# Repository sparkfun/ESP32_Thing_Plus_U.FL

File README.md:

SparkFun ESP32 Thing Plus (U.FL)
========================================

[*SparkFun ESP32 Thing Plus U.FL (WRL-18581)*](https://www.sparkfun.com/products/18581)

The [SparkFun ESP32 Thing Plus (U.FL)](https://www.sparkfun.com/products/18581) is a comprehensive development platform for [Espressif's ESP32](https://espressif.com/en/products/hardware/esp32/overview). This board has the ESP32-WROOM-32EU version of the module which contains a U.FL connector for your antenna. Like the 8266 and ESP32 Thing, the ESP32 Thing Plus is a **WiFi**-compatible microcontroller with support for **Bluetooth low-energy** (i.e BLE, BT4.0, Bluetooth Smart), a Qwiic adapter, and 21 I/O pins. Add to that a rich set of peripherals ranging from capacitive touch sensors, SD card interface, Ethernet, high-speed SPI, UART, I2S and I<sup>2</sup>C.

Upgraded and easy to use, the Esp32 Thing Plus will help make it the foundation of IoT and connected projects for many years to come.

Repository Contents
-------------------

* **/Hardware** - Eagle design files (.brd, .sch)
* **/Hardware/Production** - Production panel files (gerbers, .brd)

Documentation
--------------
* **[Hookup Guide](https://learn.sparkfun.com/tutorials/esp32-thing-plus-hookup-guide)** - Basic hookup guide for the ESP32 Thing Plus.
* **[SparkFun Fritzing repo](https://github.com/sparkfun/Fritzing_Parts)** - Fritzing diagrams for SparkFun products.
* **[SparkFun Graphical Datasheets](https://github.com/sparkfun/Graphical_Datasheets)** -Graphical Datasheets for various SparkFun products.

Product Versions
----------------
* [WRL-18581](https://www.sparkfun.com/products/18581)- Special limited edition with the u.FL
* [WRL-17381](https://www.sparkfun.com/products/17381)- v1.0, Initial Release

License Information
-------------------

This product is _**open source**_! 

Please review the LICENSE.md file for license information. 

If you have any questions or concerns on licensing, please contact technical support on our [SparkFun forums](https://forum.sparkfun.com/viewforum.php?f=152).

Distributed as-is; no warranty is given.

- Your friends at SparkFun.

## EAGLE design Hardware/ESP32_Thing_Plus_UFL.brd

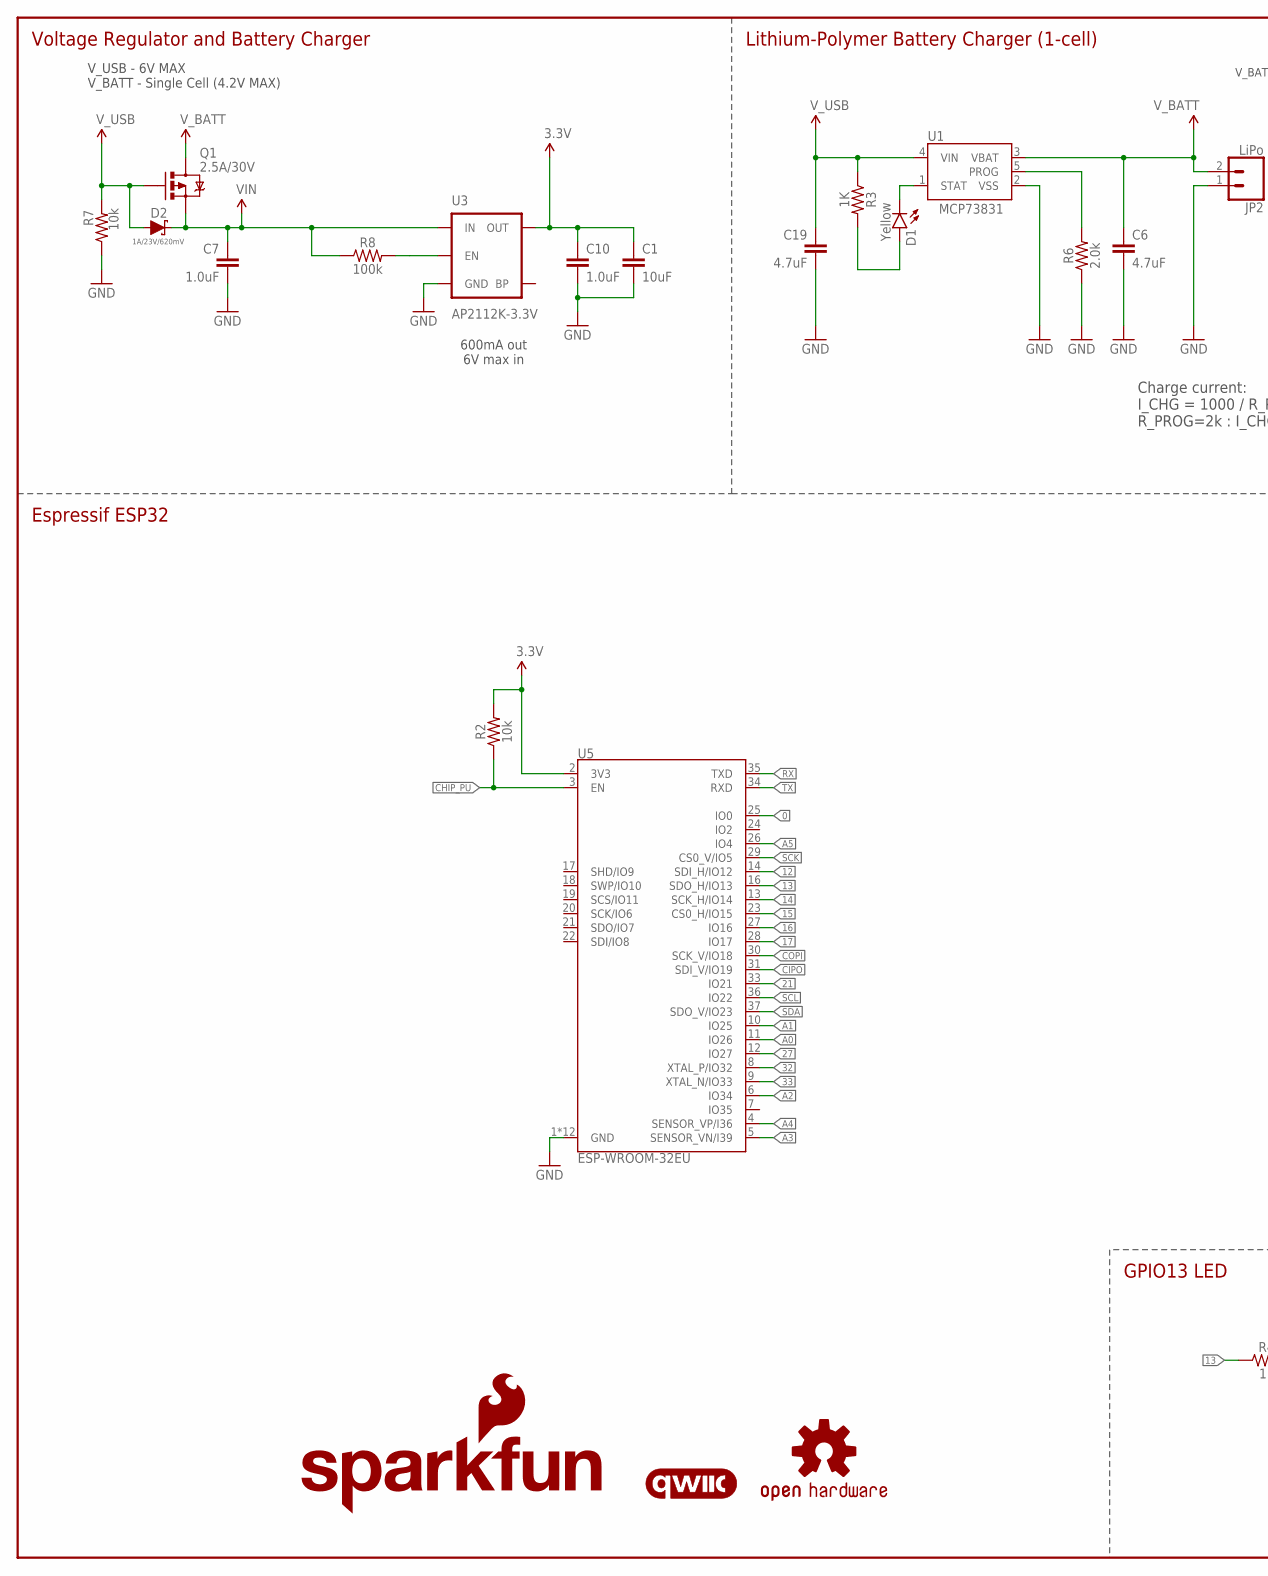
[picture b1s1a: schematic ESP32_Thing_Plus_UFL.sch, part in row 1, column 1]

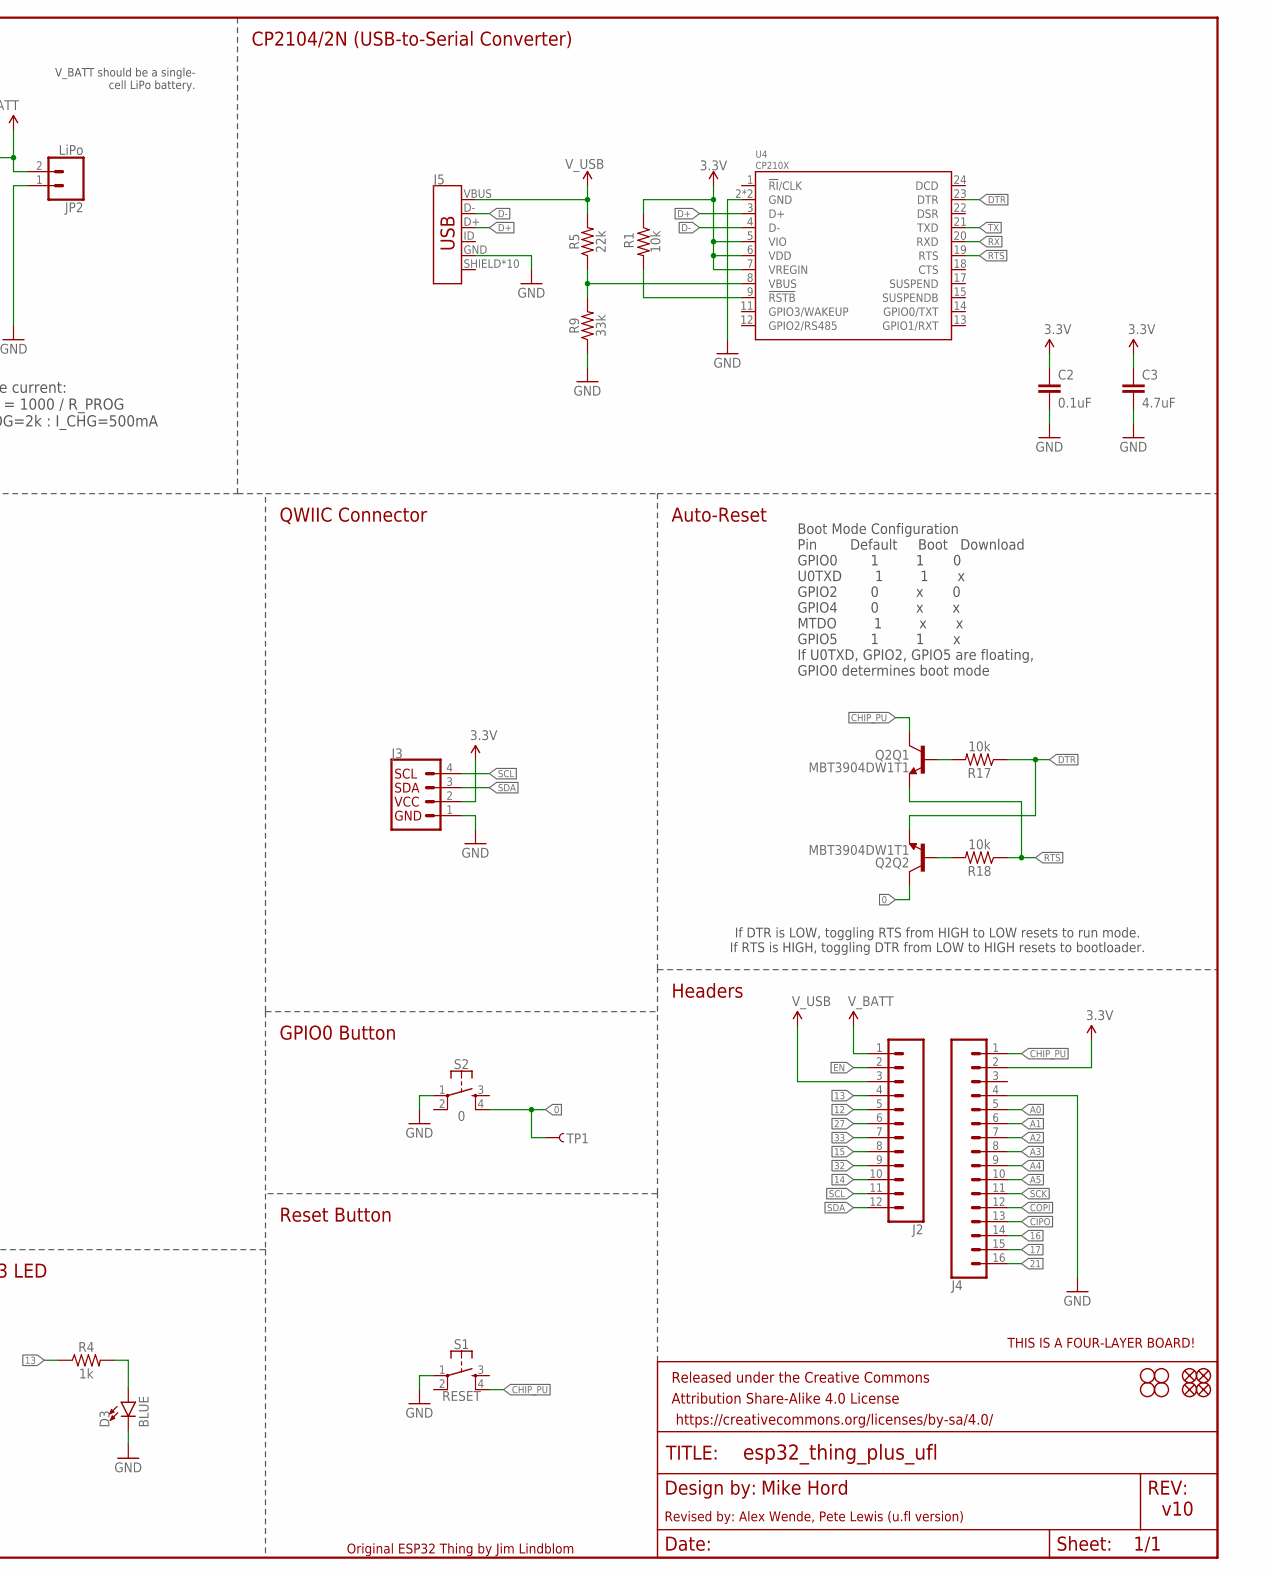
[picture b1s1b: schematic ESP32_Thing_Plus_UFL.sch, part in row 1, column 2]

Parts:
C1: 10uF; 0603
C2: 0.1uF; 0402-TIGHT
C3, C6, C19: 4.7uF; 0402-TIGHT
C7, C10: 1.0uF; 0402-TIGHT
D1: Yellow; LED-0603
D2: 1A/23V/620mV; SOD-323
D3: BLUE; LED-0603
FD1, FD2, FD3, FD4: FIDUCIALUFIDUCIAL; FIDUCIAL-MICRO
FRAME1: FRAME-LEDGER; CREATIVE_COMMONS
H1, H2, H3, H4: STAND-OFFTIGHT; STAND-OFF-TIGHT
J2: CONN_12SM_SQ_NO_SILK; 1X12_SM_SQ_NOSILK
J3: QWIIC_CONNECTORJS-1MM; 1X04_1MM_RA
J4: CONN_161X16_SM_SQ_NOSILK; 1X16_SM_SQ_NOSILK
J5: USB_MICRO-B_HALF_PTH_MILL; USB-MICROB-PTH-MILL
JP2: LiPo; JST-2-SMD
LOGO1: SFE_LOGO_NAME_FLAME.1_INCH; SFE_LOGO_NAME_FLAME_.1
LOGO2: OSHW-LOGOMINI; OSHW-LOGO-MINI
LOGO4: FOUR_LAYER_WARNING
LOGO6: QWIIC_LOGO_5MM; QWIIC_5MM
Q1: 2.5A/30V; SOT23-3@1
Q2: MBT3904DW1T1; SC70-6
R1, R2, R7, R17, R18: 10k; 0603
R3: 1K; 0603
R4: 1k; 0603
R5: 22k; 0402-TIGHT
R6: 2.0k; 0603
R8: 100k; 0402-TIGHT
R9: 33k; 0402-TIGHT
S1: RESET; TACTILE_SWITCH_SMD_4.6X2.8MM
S2: 0; TACTILE_SWITCH_SMD_4.6X2.8MM
TP1: TEST-POINTTP_15TH_THRU; TP_15TH
U1: MCP73831; SOT23-5
U3: AP2112K-3.3V; SOT23-5
U4: CP210X; QFN24
U5: ESP-WROOM-32EU; ESP-WROOM-32EU-NARROW

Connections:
0: Q2.6 (C), S2.4, TP1.P$1, U5.25 (IO0)
3.3V: C1.1, C2.1, C3.1, C10.1, J3.2, J4.2, R1.1, R2.2, U3.5 (OUT), U4.5 (VIO), U4.6 (VDD), U4.7 (VREGIN), U5.2 (3V3)
12: J2.5, U5.14 (SDI_H/IO12)
13: J2.4, R4.1, U5.16 (SDO_H/IO13)
14: J2.10, U5.13 (SCK_H/IO14)
15: J2.8, U5.23 (CS0_H/IO15)
16: J4.14, U5.27 (IO16)
17: J4.15, U5.28 (IO17)
21: J4.16, U5.33 (IO21)
27: J2.6, U5.12 (IO27)
32: J2.9, U5.8 (XTAL_P/IO32)
33: J2.7, U5.9 (XTAL_N/IO33)
A0: J4.5, U5.11 (IO26)
A1: J4.6, U5.10 (IO25)
A2: J4.7, U5.6 (IO34)
A3: J4.8, U5.5 (SENSOR_VN/I39)
A4: J4.9, U5.4 (SENSOR_VP/I36)
A5: J4.10, U5.26 (IO4)
CHG: D1.C, U1.1 (STAT)
CHIP_PU: J4.1, Q2.3 (C), R2.1, S1.4, U5.3 (EN)
CIPO: J4.13, U5.31 (SDI_V/IO19)
COPI: J4.12, U5.30 (SCK_V/IO18)
D+: J5.D+, U4.3 (D+)
D-: J5.D-, U4.4 (D-)
DTR: Q2.1 (E), R17.1, U4.23 (DTR)
EN: J2.2, R8.2, U3.3 (EN)
GND: C1.2, C2.2, C3.2, C6.2, C7.2, C10.2, C19.2, D3.C, J3.1, J4.4, J5.GND, JP2.1 (2), R6.1, R7.1, R9.1, S1.1, S2.1, U1.2 (VSS), U3.2 (GND), U4.2 (GND), U4.PAD (GND), U5.1 (GND), U5.15 (GND), U5.38 (GND), U5.GND, U5.P$1 (GND), U5.P$2 (GND), U5.P$3 (GND), U5.P$4 (GND), U5.P$5 (GND), U5.P$6 (GND), U5.P$7 (GND), U5.P$8 (GND)
unnamed: R1.2, U4.9 (!RSTB)
unnamed: D3.A, R4.2
unnamed: R5.1, R9.2, U4.8 (VBUS)
unnamed: Q2.5 (B), R17.2
unnamed: Q2.2 (B), R18.2
unnamed: R6.2, U1.5 (PROG)
unnamed: D1.A, R3.2
RTS: Q2.4 (E), R18.1, U4.19 (RTS)
RX: U4.20 (RXD), U5.35 (TXD)
SCK: J4.11, U5.29 (CS0_V/IO5)
SCL: J2.11, J3.4, U5.36 (IO22)
SDA: J2.12, J3.3, U5.37 (SDO_V/IO23)
TX: U4.21 (TXD), U5.34 (RXD)
VIN: C7.1, D2.C, Q1.2 (S), R8.1, U3.1 (IN)
V_BATT: C6.1, J2.1, JP2.2 (1), Q1.3 (D), U1.3 (VBAT)
V_USB: C19.1, D2.A, J2.3, J5.VBUS, Q1.1 (G), R3.1, R5.2, R7.2, U1.4 (VIN)

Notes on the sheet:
Boot Mode Configuration Pin Default Boot Download GPIO0 1 1 0 U0TXD 1 1 x GPIO2 0 x 0 GPIO4 0 x x MTDO 1 x x GPIO5 1 1 x If U0TXD, GPIO2, GPIO5 are floating, GPIO0 determines boot mode
CP2104/2N (USB-to-Serial Converter)
V_BATT should be a single- cell LiPo battery.
Charge current: I_CHG = 1000 / R_PROG R_PROG=2k : I_CHG=500mA
Voltage Regulator and Battery Charger
Lithium-Polymer Battery Charger (1-cell)
600mA out 6V max in
Auto-Reset
Espressif ESP32
Reset Button
Headers
v10
Original ESP32 Thing by Jim Lindblom
If DTR is LOW, toggling RTS from HIGH to LOW resets to run mode. If RTS is HIGH, toggling DTR from LOW to HIGH resets to bootloader.
QWIIC Connector
Mike Hord
GPIO13 LED
GPIO0 Button
Revised by: Alex Wende, Pete Lewis (u.fl version)
V_USB - 6V MAX V_BATT - Single Cell (4.2V MAX)

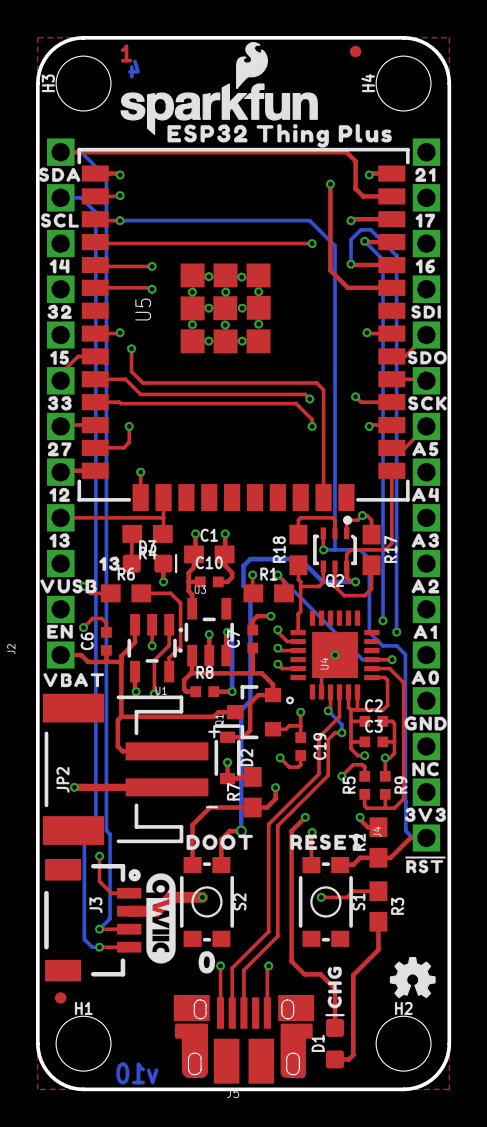
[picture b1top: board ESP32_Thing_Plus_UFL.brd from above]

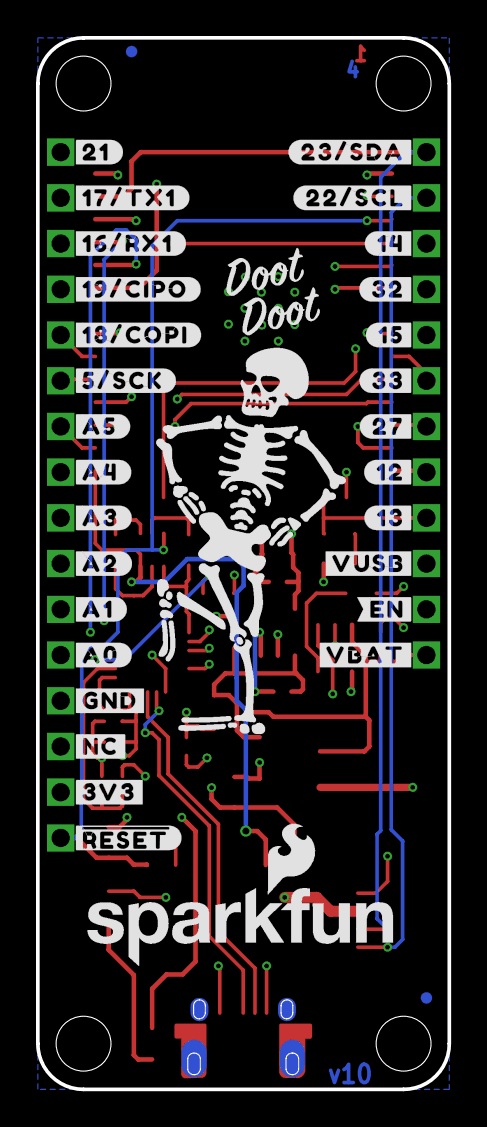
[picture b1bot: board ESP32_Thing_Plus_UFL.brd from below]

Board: 4 copper layers, 22.9 x 58.4 mm, 111 parts (30 on the bottom side), 43 nets.

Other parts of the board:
U$1: DOOT0
U$2: SDI0
U$3: #21#0
U$4: #17#TX1#0
U$5: #16#RX1#0
U$6: SDO0
U$7: #RST#0
U$8: #19#CIPO#0
U$10: #18#COPI#0
U$11: #5#SCK#0
U$12: #A5#0
U$19: #A4#0
U$21: #A3#0
U$22: #A2#0
U$24: ESP32_THING_PLUS0
U$25: SDA0
U$26: SCL0
U$27: #A1#0
U$28: #A0#0
U$31: #23#SDA#0
U$32: #GND#0
U$33: #22#SCL#0
U$34: #14#0
U$35: #32#0
U$36: #15#0
U$37: #33#0
U$38: #27#0
U$39: #12#0
U$40: #13#0
U$41: #VUSB#0
U$42: #VBAT#0
U$43: #EN#0
U$44: #NC#0
U$45: #3V3#0
U$46: ##RESET##0
U$58: 140
U$59: ORDERING_INSTRUCTIONS
U$68: 320
U$69: 150
U$70: 330
U$71: 270
U$72: 120
U$73, U$74: 130
U$75: VUSB0
U$76: EN0
U$77: VBAT0
U$78: CHG0
U$79: RESET0
U$81: 3V30
U$82: NC0
U$83: GND0
U$84: A00
U$85: A10
U$86: A20
U$87: A30
U$88: A40
U$89: A50
U$90: SCK0
U$93: 160
U$94: 170
U$95: 210
U$96: 00

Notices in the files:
parts and their libraries:
SparkFun-Resistors: Licensing: Creative Commons ShareAlike 4.0 International - https://creativecommons.org/licenses/by-sa/4.0
SparkFun-Aesthetics: Released under the Creative Commons Attribution Share-Alike 4.0 License
SparkFun-Aesthetics: https://creativecommons.org/licenses/by-sa/4.0
